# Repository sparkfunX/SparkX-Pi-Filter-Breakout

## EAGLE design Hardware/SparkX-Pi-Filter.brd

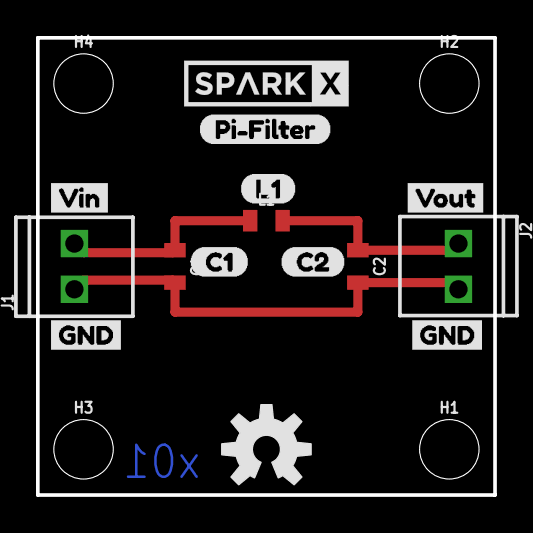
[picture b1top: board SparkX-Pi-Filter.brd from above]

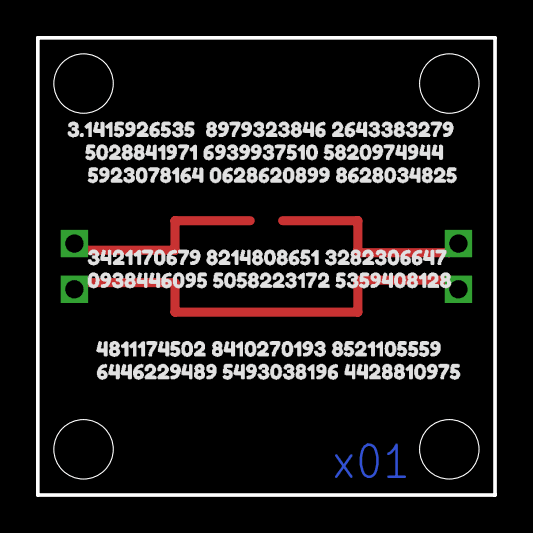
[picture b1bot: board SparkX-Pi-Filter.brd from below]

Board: 2 copper layers, 25.4 x 25.4 mm, 27 parts (7 on the bottom side), 3 nets.

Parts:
C1, C2: DNP; 0805
FRAME1: FRAME-LETTER; CREATIVE_COMMONS
H1, H2, H3, H4: STAND-OFF
J1, J2: 1X02_2.54_SCREWTERM
L1: DNP; 0805
LOGO1: OSHW-LOGOM; OSHW-LOGO-M
U$1: SPARKX-LOGO4; SPARKX-MEDIUM
U$2, U$3: GND0
U$4: PI#FILTER3
U$5: VIN1
U$6: 3#1415926535__8979323846_26433832790
U$7: 5028841971_6939937510_58209749441
U$8: 5923078164_0628620899_86280348252
U$9: 3421170679_8214808651_32823066473
U$10: 0938446095_5058223172_53594081284
U$11: 4811174502_8410270193_85211055595
U$12: 6446229489_5493038196_44288109756
U$13: VOUT2
U$14: C10
U$15: C21
U$16: L12

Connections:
GND: C1.2, C2.2, J1.P2, J2.P1
unnamed: C1.1, J1.P1, L1.1
unnamed: C2.1, J2.P2, L1.2

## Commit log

2019-01-21 Initial Schematic and Layout
    Simple Pi-Filter board initial schematic and layout commit.
2019-01-23 Added Pi to 100 Digits
    Added silk on back of board with Pi to 100 digits
2019-01-23 Changed Buzzard label for pi numbers to text
2019-01-29 Updated to meet standards
    Fixed width edge, added labels for C1, L1, C2 and Vout. Added version.
2019-02-05 Added Screw Terminals and adjusted labels
    Added Screw Terminals and adjusted labels
2019-02-05 Removing empty folders
2019-02-05 Mitre square traces. Add production gerbers.
2019-03-12 Added PDF and Zip files of project
    Added PDF and Zip files of project

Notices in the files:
parts and their libraries:
SparkFun-Capacitors: Licensing: Creative Commons ShareAlike 4.0 International - https://creativecommons.org/licenses/by-sa/4.0
SparkFun-Aesthetics: Released under the Creative Commons Attribution Share-Alike 4.0 License
SparkFun-Aesthetics: https://creativecommons.org/licenses/by-sa/4.0
